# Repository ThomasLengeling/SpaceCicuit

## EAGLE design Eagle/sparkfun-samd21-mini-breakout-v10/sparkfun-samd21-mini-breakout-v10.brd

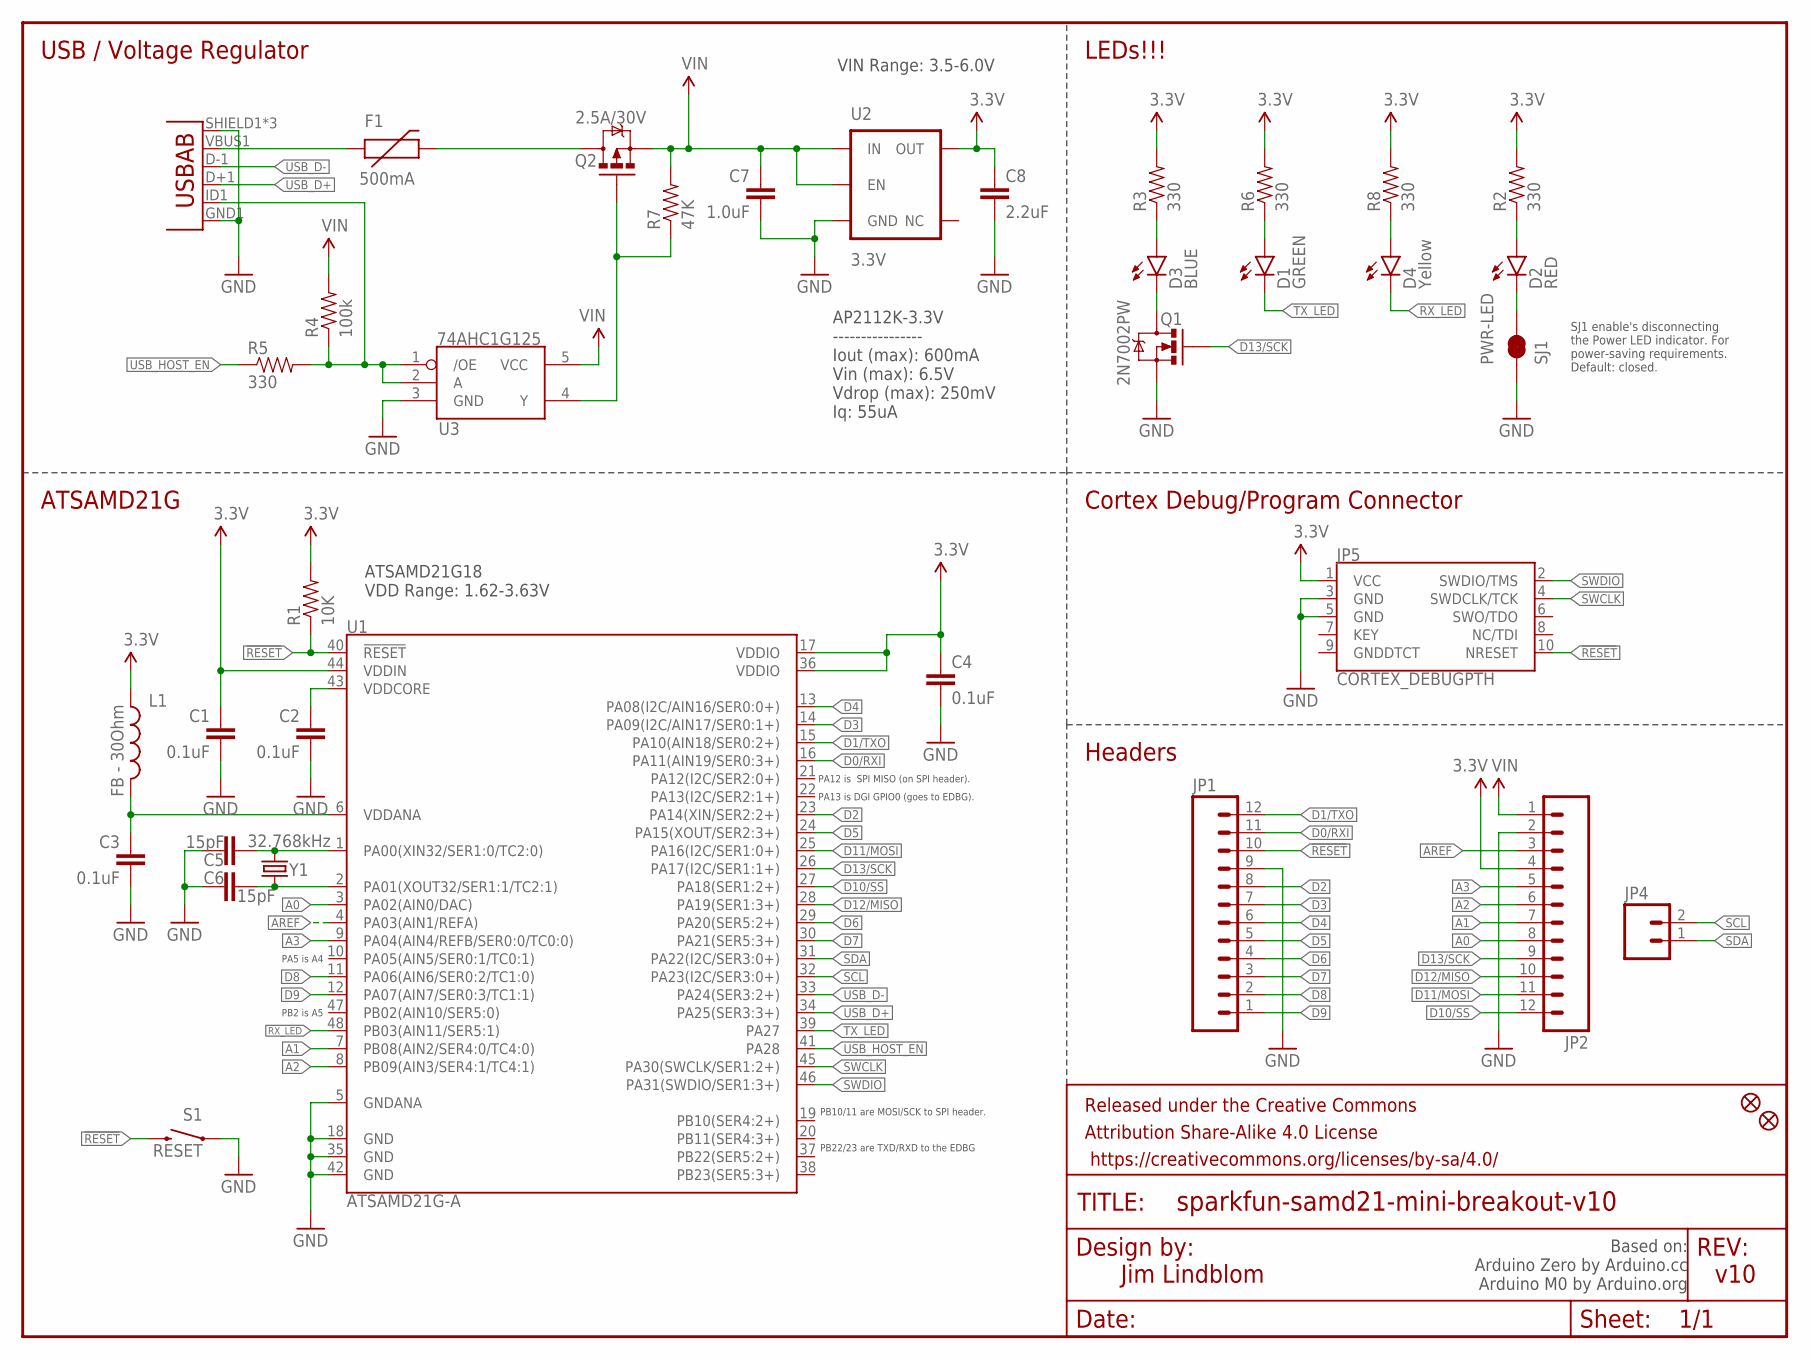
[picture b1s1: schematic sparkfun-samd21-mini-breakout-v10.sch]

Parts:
C1, C2, C3, C4: 0.1uF; 0402-CAP
C5, C6: 15pF; 0402-CAP
C7: 1.0uF; 0805-CAP
C8: 2.2uF; 0603-CAP
D1: GREEN; LED-0603
D2: RED; LED-0603
D3: BLUE; LED-0603
D4: Yellow; LED-0603
F1: 500mA; PTC-1206
FID1, FID2: FIDUCIAL1X2; FIDUCIAL-1X2
FRAME1: FRAME-LETTER; CREATIVE_COMMONS
JP1, JP2: M12NO_SILK; 1X12_NO_SILK
JP3: USB-ABCONN-11794; USB-AB-MICRO-SMD_V03
JP4: M021X02_NO_SILK; 1X02_NO_SILK
JP5: CORTEX_DEBUGPTH; 2X5-PTH-1.27MM
L1: FB - 30Ohm; 0603
Q1: 2N7002PW; SOT323
Q2: 2.5A/30V; SOT23-3
R1: 10K; 0603-RES
R2, R3, R5, R6, R8: 330; 0603-RES
R4: 100k; 0603-RES
R7: 47K; 0603-RES
S1: RESET; TACTILE_SWITCH_SMD_4.6X2.8MM
SJ1: PWR-LED; PAD-JUMPER-2-NC_BY_TRACE_NO_SILK
U1: ATSAMD21G-A; TQFP-48
U2: 3.3V; SOT23-5
U3: 74AHC1G125; SOT23-5
Y1: 32.768kHz; CRYSTAL-SMD-3.2X1.5MM

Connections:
3.3V: C1.1, C4.1, C8.1, JP2.4, JP5.1 (VCC), L1.1, R1.2, R2.2, R3.2, R6.2, R8.2, U1.17 (VDDIO), U1.36 (VDDIO), U1.44 (VDDIN), U2.5 (OUT)
!RESET: JP1.10, JP5.10 (NRESET), R1.1, S1.3 (2), S1.4 (2), U1.40 (!RESET!)
A0: JP2.8, U1.3 (PA02(AIN0/DAC))
A1: JP2.7, U1.7 (PB08(AIN2/SER4:0/TC4:0))
A2: JP2.6, U1.8 (PB09(AIN3/SER4:1/TC4:1))
A3: JP2.5, U1.9 (PA04(AIN4/REFB/SER0:0/TC0:0))
AREF: JP2.3, U1.4 (PA03(AIN1/REFA))
D0/RXI: JP1.11, U1.16 (PA11(AIN19/SER0:3+))
D1/TXO: JP1.12, U1.15 (PA10(AIN18/SER0:2+))
D2: JP1.8, U1.23 (PA14(XIN/SER2:2+))
D3: JP1.7, U1.14 (PA09(I2C/AIN17/SER0:1+))
D4: JP1.6, U1.13 (PA08(I2C/AIN16/SER0:0+))
D5: JP1.5, U1.24 (PA15(XOUT/SER2:3+))
D6: JP1.4, U1.29 (PA20(SER5:2+))
D7: JP1.3, U1.30 (PA21(SER5:3+))
D8: JP1.2, U1.11 (PA06(AIN6/SER0:2/TC1:0))
D9: JP1.1, U1.12 (PA07(AIN7/SER0:3/TC1:1))
D10/SS: JP2.12, U1.27 (PA18(SER1:2+))
D11/MOSI: JP2.11, U1.25 (PA16(I2C/SER1:0+))
D12/MISO: JP2.10, U1.28 (PA19(SER1:3+))
D13/SCK: JP2.9, Q1.1 (G), U1.26 (PA17(I2C/SER1:1+))
GND: C1.2, C2.2, C3.2, C4.2, C5.1, C6.2, C7.2, C8.2, JP1.9, JP2.2, JP3.GND1 (GND), JP3.SHIELD1 (SHIELD), JP3.SHIELD2 (SHIELD), JP3.SHIELD3 (SHIELD), JP5.3 (GND), JP5.5 (GND), Q1.2 (S), S1.1, S1.2 (1), SJ1.1, U1.5 (GNDANA), U1.18 (GND), U1.35 (GND), U1.42 (GND), U2.2 (GND), U3.3 (GND)
unnamed: F1.1, JP3.VBUS1 (VBUS)
unnamed: C5.2, U1.1 (PA00(XIN32/SER1:0/TC2:0)), Y1.P$2 (2)
unnamed: D3.C, Q1.3 (D)
unnamed: C6.1, U1.2 (PA01(XOUT32/SER1:1/TC2:1)), Y1.P$1 (1)
unnamed: D2.A, R2.1
unnamed: D3.A, R3.1
unnamed: F1.2, Q2.3 (D)
unnamed: JP3.ID1 (USBID), R4.1, R5.2, U3.1 (/OE), U3.2 (A)
unnamed: Q2.1 (G), R7.1, U3.4 (Y)
unnamed: D1.A, R6.1
unnamed: D4.A, R8.1
unnamed: D2.C, SJ1.2
RX_LED: D4.C, U1.48 (PB03(AIN11/SER5:1))
SCL: JP4.2, U1.32 (PA23(I2C/SER3:0+))
SDA: JP4.1, U1.31 (PA22(I2C/SER3:0+))
SWCLK: JP5.4 (SWDCLK/TCK), U1.45 (PA30(SWCLK/SER1:2+))
SWDIO: JP5.2 (SWDIO/TMS), U1.46 (PA31(SWDIO/SER1:3+))
TX_LED: D1.C, U1.39 (PA27)
USB_D+: JP3.D+1 (D+), U1.34 (PA25(SER3:3+))
USB_D-: JP3.D-1 (D-), U1.33 (PA24(SER3:2+))
USB_HOST_EN: R5.1, U1.41 (PA28)
VDDANA: C3.1, L1.2, U1.6 (VDDANA)
VDDCORE: C2.1, U1.43 (VDDCORE)
VIN: C7.1, JP2.1, Q2.2 (S), R4.2, R7.2, U2.1 (IN), U2.3 (EN), U3.5 (VCC)

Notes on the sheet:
PB22/23 are TXD/RXD to the EDBG
PB10/11 are MOSI/SCK to SPI header.
PA12 is SPI MISO (on SPI header).
PA13 is DGI GPIO0 (goes to EDBG).
PA5 is A4
PB2 is A5
USB / Voltage Regulator
LEDs!!!
Cortex Debug/Program Connector
Headers
ATSAMD21G
Jim Lindblom
v10
ATSAMD21G18 VDD Range: 1.62-3.63V
SJ1 enable's disconnecting the Power LED indicator. For power-saving requirements. Default: closed.
VIN Range: 3.5-6.0V
Based on: Arduino Zero by Arduino.cc Arduino M0 by Arduino.org
AP2112K-3.3V ---------------- Iout (max): 600mA Vin (max): 6.5V Vdrop (max): 250mV Iq: 55uA

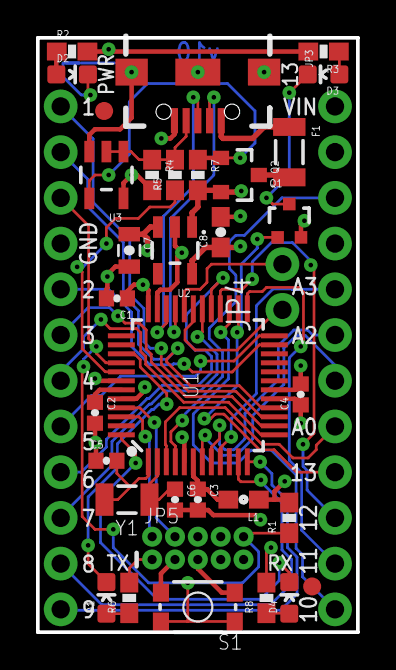
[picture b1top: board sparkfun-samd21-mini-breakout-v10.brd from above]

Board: 4 copper layers, 17.8 x 33.0 mm, 38 parts (1 on the bottom side), 46 nets.

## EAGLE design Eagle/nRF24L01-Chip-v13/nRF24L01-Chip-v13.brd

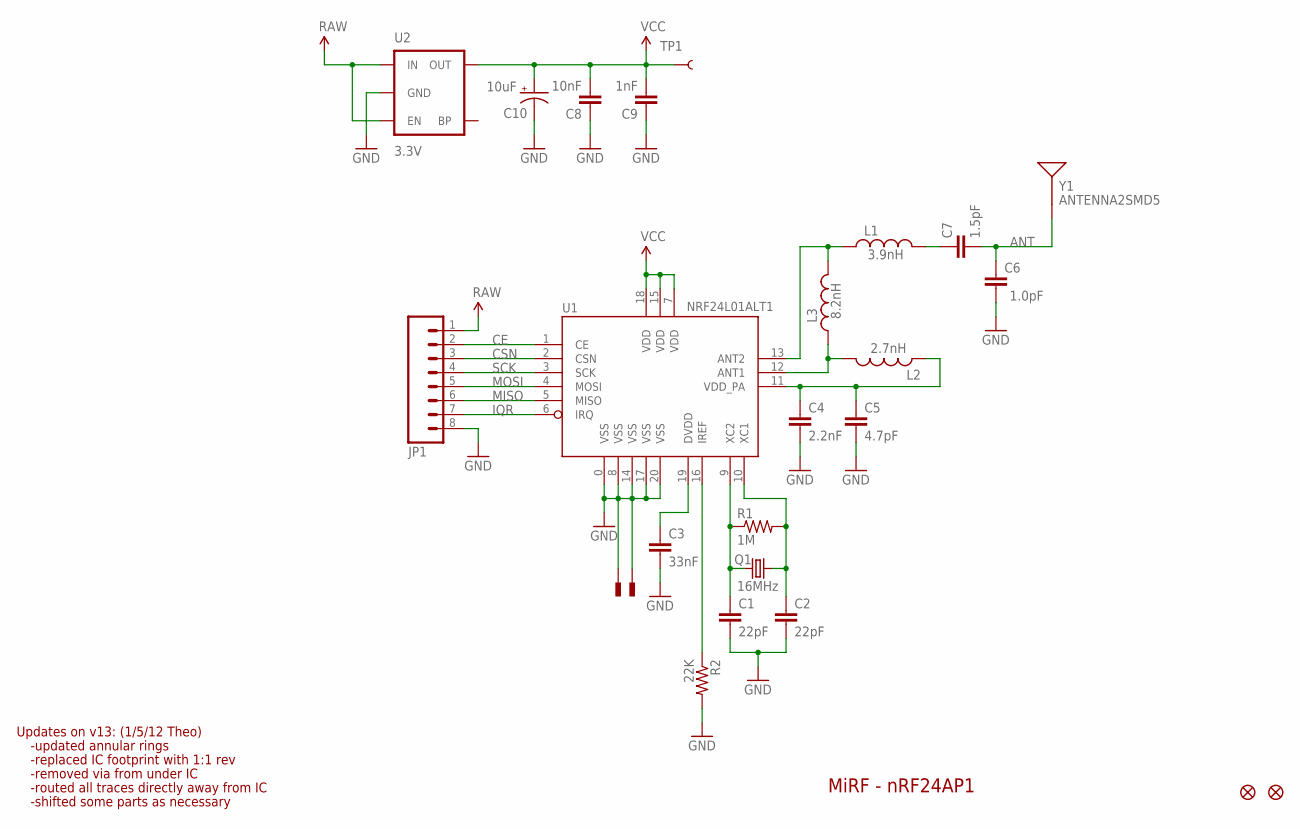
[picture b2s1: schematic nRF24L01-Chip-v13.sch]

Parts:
C1, C2: 22pF; 0402-CAP
C3: 33nF; 0402-CAP
C4: 2.2nF; 0402-CAP
C5: 4.7pF; 0402-CAP
C6: 1.0pF; 0402-CAP
C7: 1.5pF; 0402-CAP
C8: 10nF; 0402-CAP
C9: 1nF; 0402-CAP
C10: 10uF; EIA3216
JP1: M081X08; 1X08
JP2, JP3: FIDUCIALUFIDUCIAL; MICRO-FIDUCIAL
L1: 3.9nH; C0402
L2: 2.7nH; C0402
L3: 8.2nH; C0402
Q1: 16MHz; CRYSTAL-SMD-5X3
R1: 1M; 0402-RES
R2: 22K; 0402-RES
TP1: TEST-POINT3X5; PAD.03X.05
U1: NRF24L01ALT1; QFN20_ALT1
U2: 3.3V; SOT23-5
U$1, U$4: PAD; PAD-0.008
Y1: ANTENNA2SMD5; ANTENNA-CHIP5

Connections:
ANT: C6.2, C7.2, Y1.FEED
CE: JP1.2, U1.1 (CE)
CSN: JP1.3, U1.2 (CSN)
GND: C1.2, C2.2, C3.2, C4.2, C5.2, C6.1, C8.1, C9.1, C10.C (-), JP1.8, R2.2, U1.0 (VSS), U1.8 (VSS), U1.14 (VSS), U1.17 (VSS), U1.20 (VSS), U2.2 (GND), U$1.P$1, U$4.P$1
IQR: JP1.7, U1.6 (IRQ)
MISO: JP1.6, U1.5 (MISO)
MOSI: JP1.5, U1.4 (MOSI)
unnamed: C1.1, Q1.1, R1.1, U1.9 (XC2)
unnamed: C2.1, Q1.3 (2), R1.2, U1.10 (XC1)
unnamed: L2.2, L3.1, U1.12 (ANT1)
unnamed: R2.1, U1.16 (IREF)
unnamed: C3.1, U1.19 (DVDD)
unnamed: L1.1, L3.2, U1.13 (ANT2)
unnamed: C4.1, C5.1, L2.1, U1.11 (VDD_PA)
unnamed: C7.1, L1.2
RAW: JP1.1, U2.1 (IN), U2.3 (EN)
SCK: JP1.4, U1.3 (SCK)
VCC: C8.2, C9.2, C10.A (+), TP1.P$1, U1.7 (VDD), U1.15 (VDD), U1.18 (VDD), U2.5 (OUT)

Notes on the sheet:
MiRF - nRF24AP1
Updates on v13: (1/5/12 Theo)
-updated annular rings
-replaced IC footprint with 1:1 rev
-removed via from under IC
-routed all traces directly away from IC
-shifted some parts as necessary

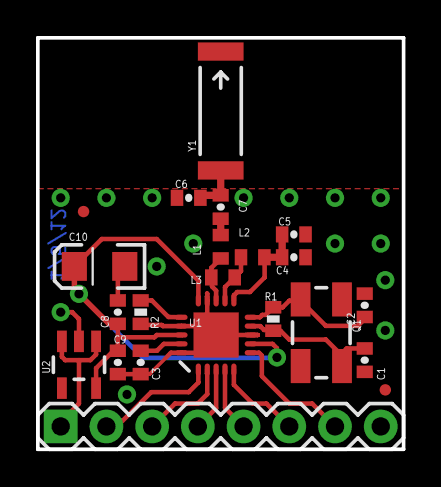
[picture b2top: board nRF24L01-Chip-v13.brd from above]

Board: 2 copper layers, 20.3 x 22.9 mm, 25 parts (1 on the bottom side), 18 nets.

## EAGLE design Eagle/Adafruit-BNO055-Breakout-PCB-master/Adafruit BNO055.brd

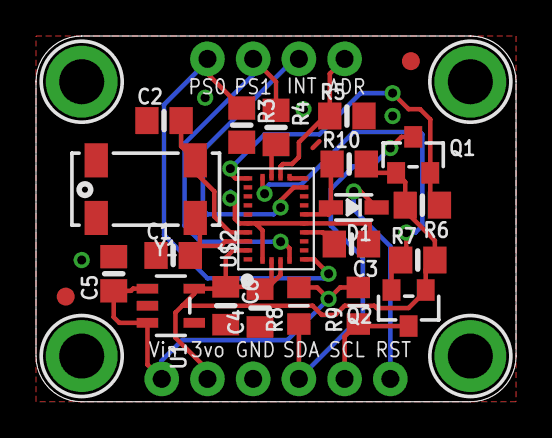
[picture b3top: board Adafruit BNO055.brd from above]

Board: 2 copper layers, 26.7 x 20.3 mm, 28 parts (0 on the bottom side), 16 nets.

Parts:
C1, C2: 22pF; 0805-NO
C3: 0.1uF; 0805-NO
C4: 0.1uF; 0805_10MGAP
C5: 10uF; 0805-NO
C6: 10uF; 0805_10MGAP
D1: 1n4148; SOD-323
FID1, FID2: FIDUCIAL""; FIDUCIAL_1MM
JP1: 1X06_ROUND_76
JP2: 1X04_ROUND_76
Q1, Q2: BSS138; SOT23-WIDE
R3, R4, R5, R6, R7, R10: 10K; 0805-NO
R8, R9: 10K; _0805MP
U1: MIC5225-3.3; SOT23-5
U$2: BNO055
U$29, U$30, U$31, U$32: MOUNTINGHOLE2.5_THICK; MOUNTINGHOLE_2.5_PLATED_THICK
Y1: 32.768kHz; CRYSTAL_8X3.8

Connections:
3.3V: C4.2, C6.1, JP1.2, Q1.1, Q2.1, R6.2, R7.2, R10.2, U1.5, U$2.3, U$2.4, U$2.28
5.0V: C5.1, JP1.1, R8.2, R9.2, U1.1, U1.3
GND: C1.1, C2.1, C3.1, C4.1, C5.2, C6.2, JP1.3, R3.2, R4.2, R5.2, U1.2, U$2.2, U$2.10, U$2.15, U$2.16, U$2.18, U$2.25
I2CADDR_3V: JP2.4, R5.1, U$2.17
INT_3V: JP2.3, U$2.14
unnamed: C1.2, U$2.27, Y1.P$4
unnamed: C2.2, U$2.26, Y1.P$1
unnamed: C3.2, U$2.9
NRESET_3V: D1.A, R10.1, U$2.11
PS0_3V: JP2.1, R3.1, U$2.6
PS1_3V: JP2.2, R4.1, U$2.5
RST_5V: D1.C, JP1.6
SCL_3V: Q2.2, R7.1, U$2.19
SCL_5V: JP1.5, Q2.3, R9.1
SDA_3V: Q1.2, R6.1, U$2.20
SDA_5V: JP1.4, Q1.3, R8.1

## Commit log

2018-11-27 circuits uploaded
2018-11-27 clean circuits

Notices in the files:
parts and their libraries:
microbuilder: This work is placed in the public domain, and may be freely used for commercial and non-commercial work with the following conditions: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
SparkFun-Connectors: Licensing: Creative Commons ShareAlike 4.0 International - https://creativecommons.org/licenses/by-sa/4.0
